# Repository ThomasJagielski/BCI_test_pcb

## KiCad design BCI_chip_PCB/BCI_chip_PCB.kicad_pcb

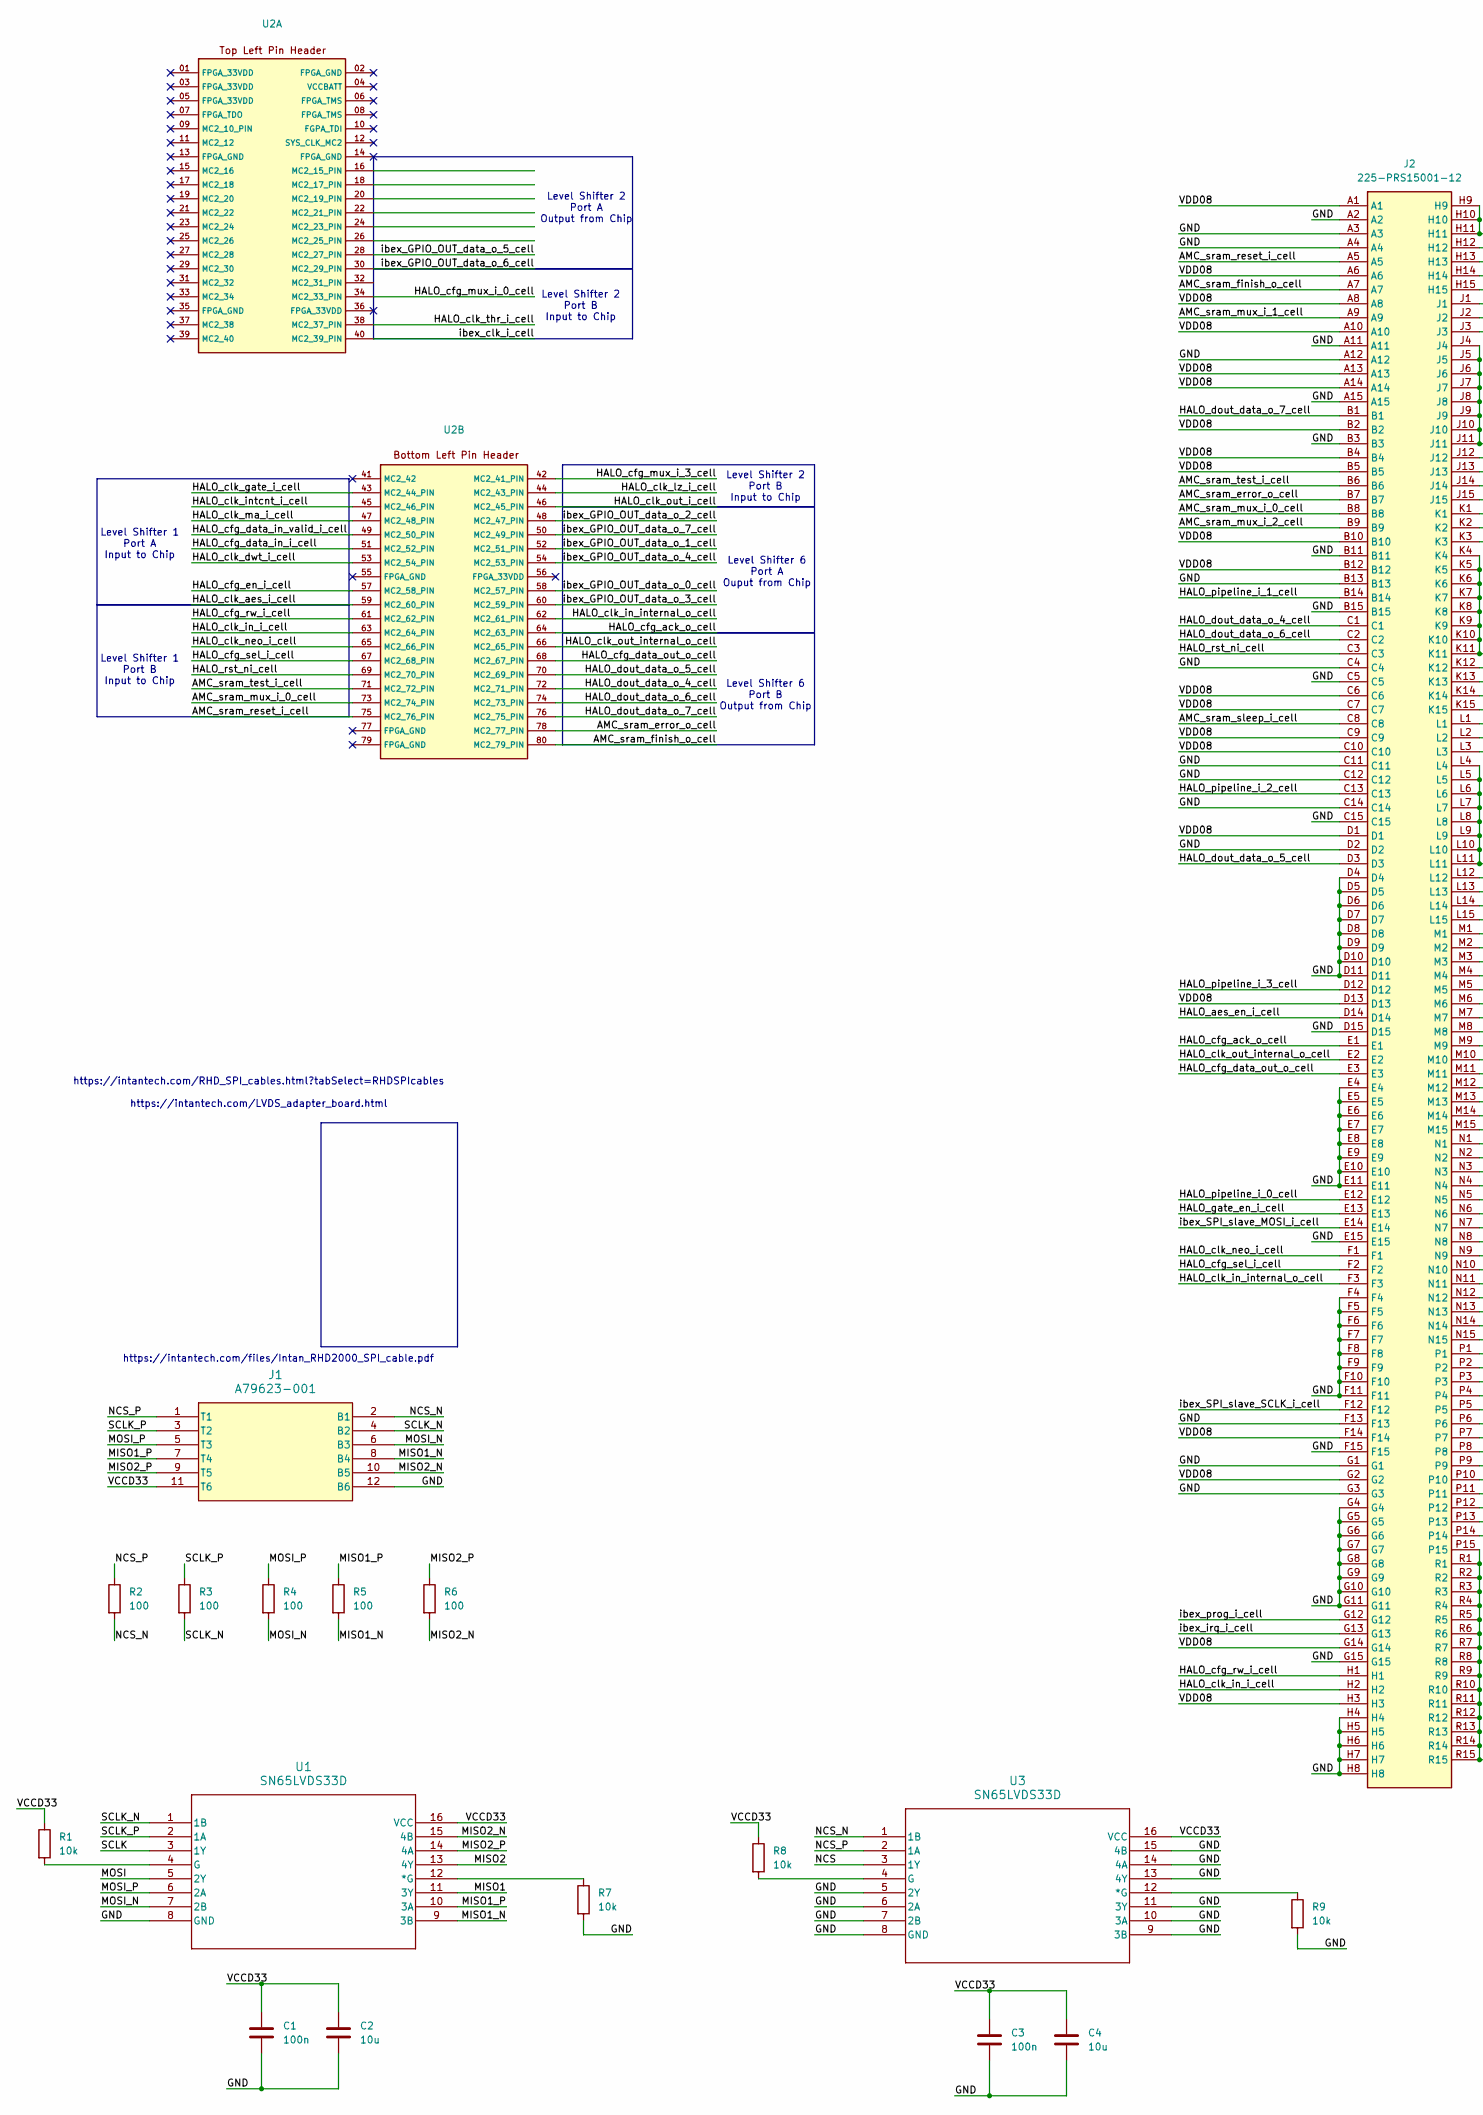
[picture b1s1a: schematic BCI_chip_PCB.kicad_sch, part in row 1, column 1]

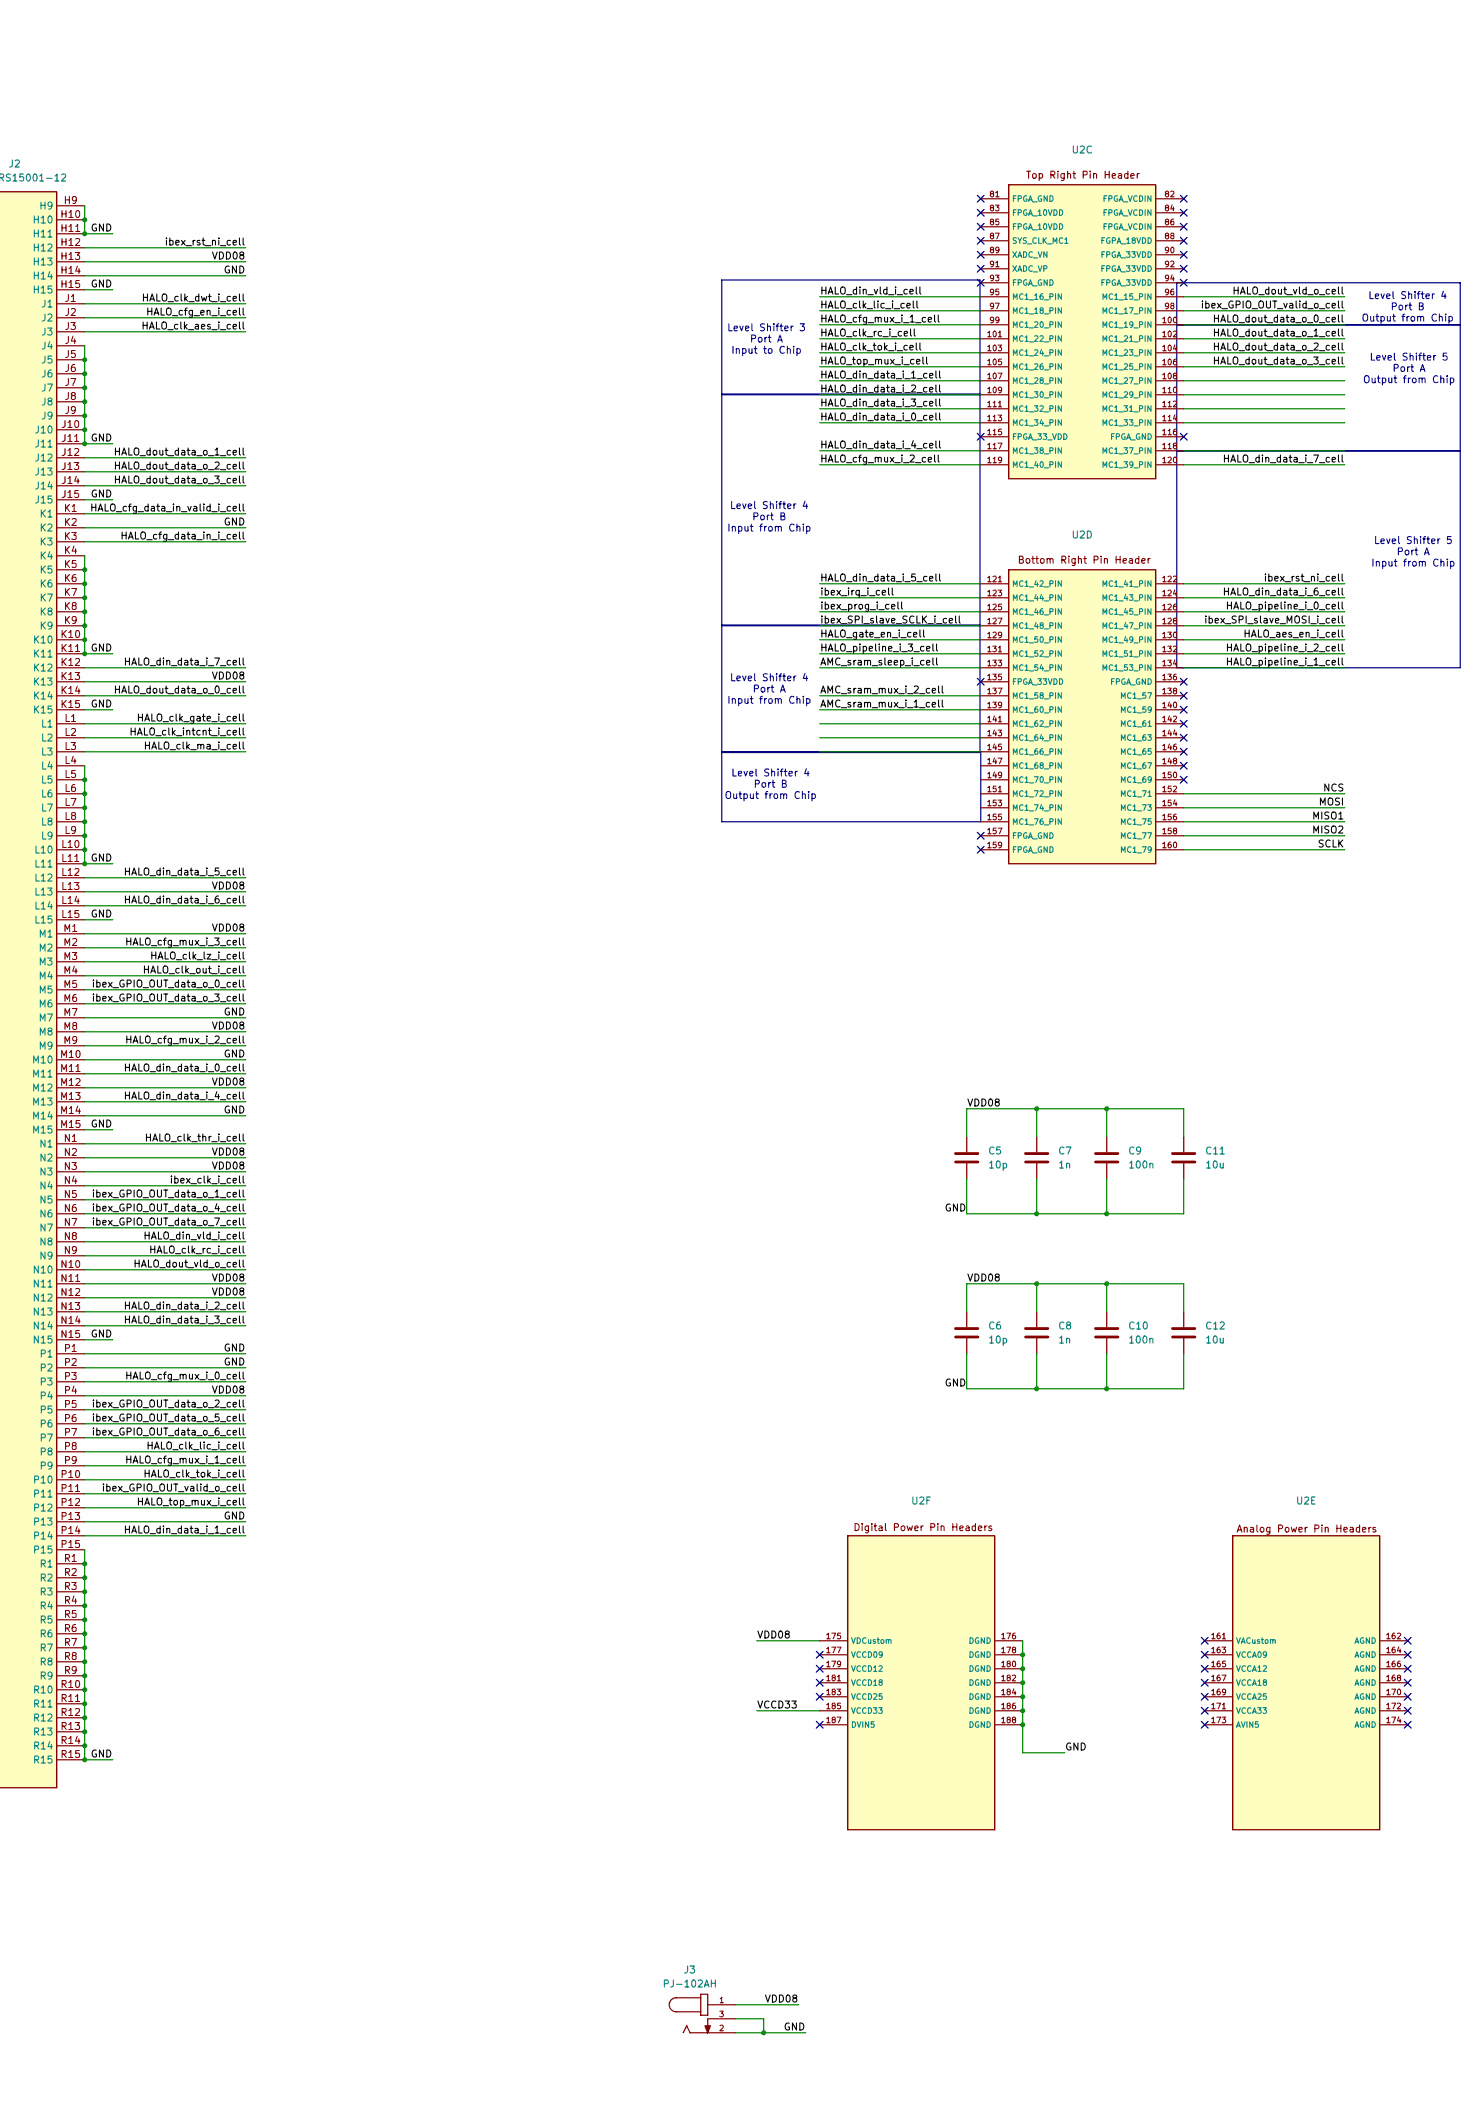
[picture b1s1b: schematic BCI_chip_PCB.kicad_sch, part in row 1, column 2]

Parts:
C1, C3, C9, C10: 100n; C_0603_1608Metric
C2, C4, C11, C12: 10u; C_0603_1608Metric
C5, C6: 10p; C_0603_1608Metric
C7, C8: 1n; C_0603_1608Metric
J1: A79623-001; CONN_A79623-001_OMN
J2: 225-PRS15001-12; 225PRS1500112; Mouser Part Number 535-225-PRS15001-12
J3: PJ-102AH; BarrelJack_CUI_PJ-102AH_Horizontal; PART_REV 1.02
R1, R7, R8, R9: 10k; R_0805_2012Metric
R2, R3, R4, R5, R6: 100; R_0805_2012Metric
U1, U3: SN65LVDS33D; D16
U2: avlsi_power_board_opal_kelly

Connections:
/AMC_sram_error_o_cell: J2.B7, U2.78 (MC2_77_PIN)
/AMC_sram_finish_o_cell: J2.A7, U2.80 (MC2_79_PIN)
/AMC_sram_mux_i_0_cell: J2.B8, U2.73 (MC2_74_PIN)
/AMC_sram_mux_i_1_cell: J2.A9, U2.139 (MC1_60_PIN)
/AMC_sram_mux_i_2_cell: J2.B9, U2.137 (MC1_58_PIN)
/AMC_sram_reset_i_cell: J2.A5, U2.75 (MC2_76_PIN)
/AMC_sram_sleep_i_cell: J2.C8, U2.133 (MC1_54_PIN)
/AMC_sram_test_i_cell: J2.B6, U2.71 (MC2_72_PIN)
/GND: C1.2, C2.2, C3.2, C4.2, C5.2, C6.2, C7.2, C8.2, C9.2, C10.2, C11.2, C12.2, J1.12 (B6), J2.A2, J2.A3, J2.A4, J2.A11, J2.A12, J2.A15, J2.B3, J2.B11, J2.B13, J2.B15, J2.C4, J2.C5, J2.C11, J2.C12, J2.C14, J2.C15, J2.D2, J2.D4, J2.D5, J2.D6, J2.D7, J2.D8, J2.D9, J2.D10, J2.D11, J2.D15, J2.E4, J2.E5, J2.E6, J2.E7, J2.E8, J2.E9, J2.E10, J2.E11, J2.E15, J2.F4, J2.F5, J2.F6, J2.F7, J2.F8, J2.F9, J2.F10, J2.F11, J2.F13, J2.F15, J2.G1, J2.G3, J2.G4, J2.G5, J2.G6, J2.G7, J2.G8, J2.G9, J2.G10, J2.G11, J2.G15, J2.H4, J2.H5, J2.H6, J2.H7, J2.H8, J2.H9, J2.H10, J2.H11, J2.H14, J2.H15, J2.J4, J2.J5, J2.J6, J2.J7, J2.J8, J2.J9, J2.J10, J2.J11, J2.J15, J2.K2, J2.K4, J2.K5, J2.K6, J2.K7, J2.K8, J2.K9, J2.K10, J2.K11, J2.K15, J2.L4, J2.L5, J2.L6, J2.L7, J2.L8, J2.L9, J2.L10, J2.L11, J2.L15, J2.M7, J2.M10, J2.M14, J2.M15, J2.N15, J2.P1, J2.P2, J2.P13, J2.P15, J2.R1, J2.R2, J2.R3, J2.R4, J2.R5, J2.R6, J2.R7, J2.R8, J2.R9, J2.R10, J2.R11, J2.R12, J2.R13, J2.R14, J2.R15, J3.2, J3.3, R7.2, R9.2, U1.8 (GND), U2.176 (DGND), U2.178 (DGND), U2.180 (DGND), U2.182 (DGND), U2.184 (DGND), U2.186 (DGND), U2.188 (DGND), U3.5 (2Y), U3.6 (2A), U3.7 (2B), U3.8 (GND), U3.9 (3B), U3.10 (3A), U3.11 (3Y), U3.13 (4Y), U3.14 (4A), U3.15 (4B)
/HALO_aes_en_i_cell: J2.D14, U2.130 (MC1_49_PIN)
/HALO_cfg_ack_o_cell: J2.E1, U2.64 (MC2_63_PIN)
/HALO_cfg_data_in_i_cell: J2.K3, U2.51 (MC2_52_PIN)
/HALO_cfg_data_in_valid_i_cell: J2.K1, U2.49 (MC2_50_PIN)
/HALO_cfg_data_out_o_cell: J2.E3, U2.68 (MC2_67_PIN)
/HALO_cfg_en_i_cell: J2.J2, U2.57 (MC2_58_PIN)
/HALO_cfg_mux_i_0_cell: J2.P3, U2.34 (MC2_33_PIN)
/HALO_cfg_mux_i_1_cell: J2.P9, U2.99 (MC1_20_PIN)
/HALO_cfg_mux_i_2_cell: J2.M9, U2.119 (MC1_40_PIN)
/HALO_cfg_mux_i_3_cell: J2.M2, U2.42 (MC2_41_PIN)
/HALO_cfg_rw_i_cell: J2.H1, U2.61 (MC2_62_PIN)
/HALO_cfg_sel_i_cell: J2.F2, U2.67 (MC2_68_PIN)
/HALO_clk_aes_i_cell: J2.J3, U2.59 (MC2_60_PIN)
/HALO_clk_dwt_i_cell: J2.J1, U2.53 (MC2_54_PIN)
/HALO_clk_gate_i_cell: J2.L1, U2.43 (MC2_44_PIN)
/HALO_clk_in_i_cell: J2.H2, U2.63 (MC2_64_PIN)
/HALO_clk_in_internal_o_cell: J2.F3, U2.62 (MC2_61_PIN)
/HALO_clk_intcnt_i_cell: J2.L2, U2.45 (MC2_46_PIN)
/HALO_clk_lic_i_cell: J2.P8, U2.97 (MC1_18_PIN)
/HALO_clk_lz_i_cell: J2.M3, U2.44 (MC2_43_PIN)
/HALO_clk_ma_i_cell: J2.L3, U2.47 (MC2_48_PIN)
/HALO_clk_neo_i_cell: J2.F1, U2.65 (MC2_66_PIN)
/HALO_clk_out_i_cell: J2.M4, U2.46 (MC2_45_PIN)
/HALO_clk_out_internal_o_cell: J2.E2, U2.66 (MC2_65_PIN)
/HALO_clk_rc_i_cell: J2.N9, U2.101 (MC1_22_PIN)
/HALO_clk_thr_i_cell: J2.N1, U2.38 (MC2_37_PIN)
/HALO_clk_tok_i_cell: J2.P10, U2.103 (MC1_24_PIN)
/HALO_din_data_i_0_cell: J2.M11, U2.113 (MC1_34_PIN)
/HALO_din_data_i_1_cell: J2.P14, U2.107 (MC1_28_PIN)
/HALO_din_data_i_2_cell: J2.N13, U2.109 (MC1_30_PIN)
/HALO_din_data_i_3_cell: J2.N14, U2.111 (MC1_32_PIN)
/HALO_din_data_i_4_cell: J2.M13, U2.117 (MC1_38_PIN)
/HALO_din_data_i_5_cell: J2.L12, U2.121 (MC1_42_PIN)
/HALO_din_data_i_6_cell: J2.L14, U2.124 (MC1_43_PIN)
/HALO_din_data_i_7_cell: J2.K12, U2.120 (MC1_39_PIN)
/HALO_din_vld_i_cell: J2.N8, U2.95 (MC1_16_PIN)
/HALO_dout_data_o_0_cell: J2.K14, U2.100 (MC1_19_PIN)
/HALO_dout_data_o_1_cell: J2.J12, U2.102 (MC1_21_PIN)
/HALO_dout_data_o_2_cell: J2.J13, U2.104 (MC1_23_PIN)
/HALO_dout_data_o_3_cell: J2.J14, U2.106 (MC1_25_PIN)
/HALO_dout_data_o_4_cell: J2.C1, U2.72 (MC2_71_PIN)
/HALO_dout_data_o_5_cell: J2.D3, U2.70 (MC2_69_PIN)
/HALO_dout_data_o_6_cell: J2.C2, U2.74 (MC2_73_PIN)
/HALO_dout_data_o_7_cell: J2.B1, U2.76 (MC2_75_PIN)
/HALO_dout_vld_o_cell: J2.N10, U2.96 (MC1_15_PIN)
/HALO_gate_en_i_cell: J2.E13, U2.129 (MC1_50_PIN)
/HALO_pipeline_i_0_cell: J2.E12, U2.126 (MC1_45_PIN)
/HALO_pipeline_i_1_cell: J2.B14, U2.134 (MC1_53_PIN)
/HALO_pipeline_i_2_cell: J2.C13, U2.132 (MC1_51_PIN)
/HALO_pipeline_i_3_cell: J2.D12, U2.131 (MC1_52_PIN)
/HALO_rst_ni_cell: J2.C3, U2.69 (MC2_70_PIN)
/HALO_top_mux_i_cell: J2.P12, U2.105 (MC1_26_PIN)
/MISO1: U1.11 (3Y), U2.156 (MC1_75)
/MISO1_N: J1.8 (B4), R5.2, U1.9 (3B)
/MISO1_P: J1.7 (T4), R5.1, U1.10 (3A)
/MISO2: U1.13 (4Y), U2.158 (MC1_77)
/MISO2_N: J1.10 (B5), R6.2, U1.15 (4B)
/MISO2_P: J1.9 (T5), R6.1, U1.14 (4A)
/MOSI: U1.5 (2Y), U2.154 (MC1_73)
/MOSI_N: J1.6 (B3), R4.2, U1.7 (2B)
/MOSI_P: J1.5 (T3), R4.1, U1.6 (2A)
/NCS: U2.152 (MC1_71), U3.3 (1Y)
/NCS_N: J1.2 (B1), R2.2, U3.1 (1B)
/NCS_P: J1.1 (T1), R2.1, U3.2 (1A)
/SCLK: U1.3 (1Y), U2.160 (MC1_79)
/SCLK_N: J1.4 (B2), R3.2, U1.1 (1B)
/SCLK_P: J1.3 (T2), R3.1, U1.2 (1A)
/VCCD33: C1.1, C2.1, C3.1, C4.1, J1.11 (T6), R1.1, R8.1, U1.16 (VCC), U2.185 (VCCD33), U3.16 (VCC)
/VDD08: C5.1, C6.1, C7.1, C8.1, C9.1, C10.1, C11.1, C12.1, J2.A1, J2.A6, J2.A8, J2.A10, J2.A13, J2.A14, J2.B2, J2.B4, J2.B5, J2.B10, J2.B12, J2.C6, J2.C7, J2.C9, J2.C10, J2.D1, J2.D13, J2.F14, J2.G2, J2.G14, J2.H3, J2.H13, J2.K13, J2.L13, J2.M1, J2.M8, J2.M12, J2.N2, J2.N3, J2.N11, J2.N12, J2.P4, J3.1, U2.175 (VDCustom)
/ibex_GPIO_OUT_data_o_0_cell: J2.M5, U2.58 (MC2_57_PIN)
/ibex_GPIO_OUT_data_o_1_cell: J2.N5, U2.52 (MC2_51_PIN)
/ibex_GPIO_OUT_data_o_2_cell: J2.P5, U2.48 (MC2_47_PIN)
/ibex_GPIO_OUT_data_o_3_cell: J2.M6, U2.60 (MC2_59_PIN)
/ibex_GPIO_OUT_data_o_4_cell: J2.N6, U2.54 (MC2_53_PIN)
/ibex_GPIO_OUT_data_o_5_cell: J2.P6, U2.28 (MC2_27_PIN)
/ibex_GPIO_OUT_data_o_6_cell: J2.P7, U2.30 (MC2_29_PIN)
/ibex_GPIO_OUT_data_o_7_cell: J2.N7, U2.50 (MC2_49_PIN)
/ibex_GPIO_OUT_valid_o_cell: J2.P11, U2.98 (MC1_17_PIN)
/ibex_SPI_slave_MOSI_i_cell: J2.E14, U2.128 (MC1_47_PIN)
/ibex_SPI_slave_SCLK_i_cell: J2.F12, U2.127 (MC1_48_PIN)
/ibex_clk_i_cell: J2.N4, U2.40 (MC2_39_PIN)
/ibex_irq_i_cell: J2.G13, U2.123 (MC1_44_PIN)
/ibex_prog_i_cell: J2.G12, U2.125 (MC1_46_PIN)
/ibex_rst_ni_cell: J2.H12, U2.122 (MC1_41_PIN)
unnamed: R7.1, U1.12 (*G)
unnamed: R1.2, U1.4 (G)
unnamed: R9.1, U3.12 (*G)
unnamed: R8.2, U3.4 (G)

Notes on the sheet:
Level Shifter 4 Port B Output from Chip
https://intantech.com/files/Intan_RHD2000_SPI_cable.pdf
Level Shifter 2 Port A Output from Chip
Level Shifter 2 Port B Input to Chip
Level Shifter 4 Port B Input from Chip
Level Shifter 6 Port A Ouput from Chip
Level Shifter 5 Port A Input from Chip
Level Shifter 5 Port A Output from Chip
Level Shifter 6 Port B Output from Chip
Level Shifter 1 Port B Input to Chip
Level Shifter 4 Port A Input from Chip
Level Shifter 1 Port A Input to Chip
https://intantech.com/RHD_SPI_cables.html?tabSelect=RHDSPIcables https://intantech.com/LVDS_adapter_board.html
Level Shifter 3 Port A Input to Chip

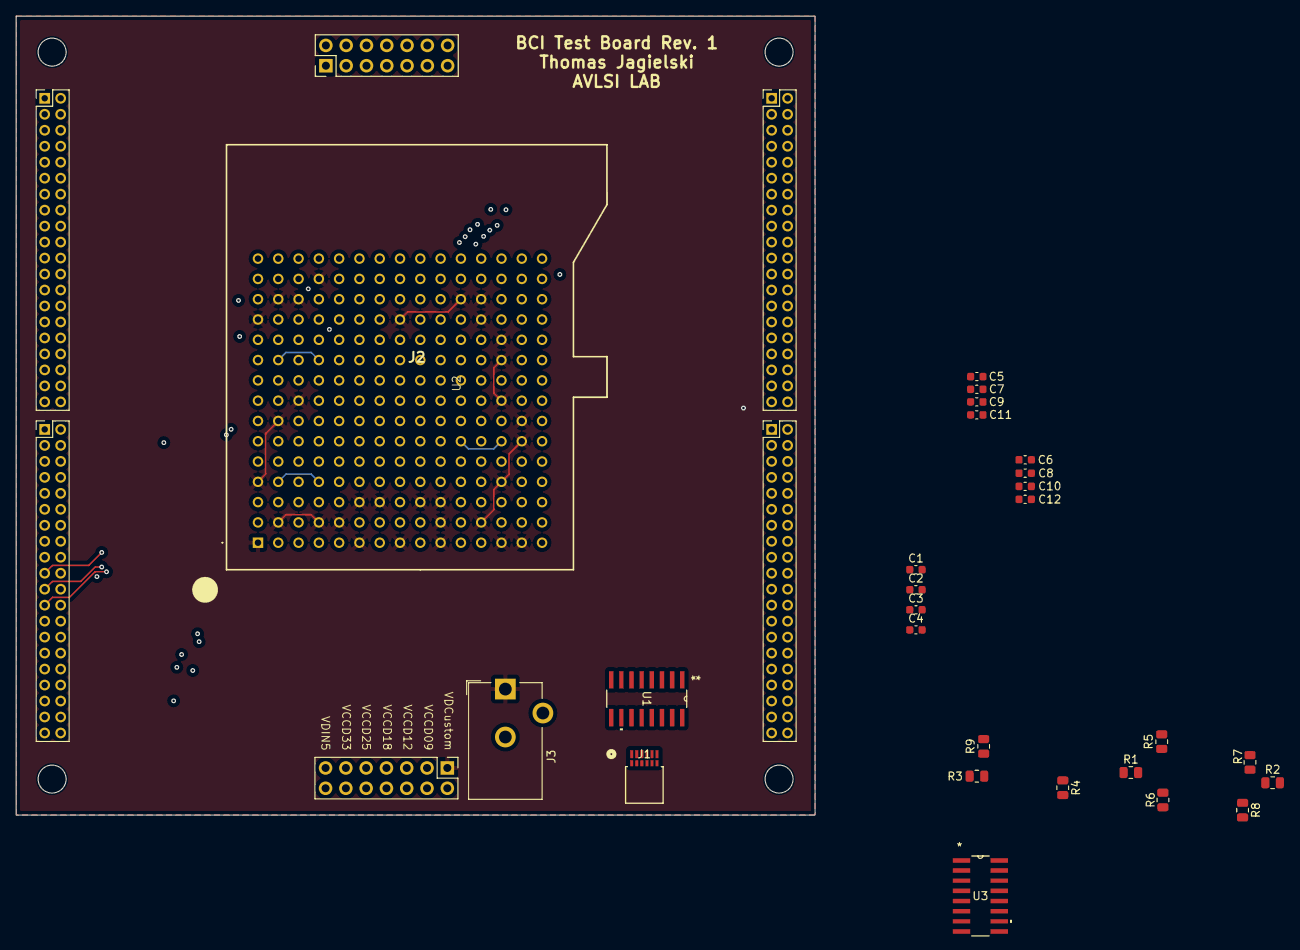
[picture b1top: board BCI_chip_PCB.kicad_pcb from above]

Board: 4 copper layers, 100.0 x 100.0 mm, 27 parts (0 on the bottom side), 97 nets.

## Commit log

2025-02-06 Add updated board
